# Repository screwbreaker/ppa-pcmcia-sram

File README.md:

# SAKURA, Amiga pcmcia sram
4MB of Fast RAM for unexpanded Amiga 600/1200.
Original desig by Jarosław Bieliński and Radosław Kujawa.
The informations about the original version of this board can be found here: https://github.com/Sakura-IT/ppa-pcmcia-sram

Since the original version, some components, like the RAM, are became difficult to find, so, many revisions of this board was made in order to use available components.
In 2018 the project was updated again and ported to KiCad by jensma: https://github.com/jensma/ppa-pcmcia-sram
This revision is based on his work.

### Summary
Some components like the RAM are available but not cheap. On the jensma revision also the PCB was not cheap, because he used small tracks and vias.
The main goal of this revision is to made the PCB as cheaper as possible. This make this expansion a little more affordable.

#### BOM
- C14,C3,C5,C6,C7,C8,C9,C10,C11,C12,C13,C4 100nF 0805 ceramic capacitor
- C1,C2: >=10uF >=6,3V 1206 tantalum capacitor
- U1: LM1117-3.3 voltage regulator
- IC2,IC3, IC4 74LCX245MTC
- IC5,IC6,IC7: 74LCX541TTR
- IC1: AS6C3216-55, SRAM
- IC8: XC9536XL_44VQ CPLD
- PCMCIA connector 95622-004LF
- SW1: SW_SPDT_CK-JS102011SAQN

### Installation
Since this board don't have a proper PCMCIA case it must be inserted carefully.
Do not apply too much force, or the pin iside the Amiga connector can be damaged.
There is a maker on the board to identify the upper side.

### License
This board is Open Hardware. If you make any modifications to the board, please contribute them back.

### Disclaimer
This board is provided to you 'as is' and without any express or implied warranties whatsoever with respect to its functionality, operability or use, including, without limitation, any implied warranties of merchantability, fitness for a particular purpose or infringement. We expressly disclaim any liability whatsoever for any direct, indirect, consequential, incidental or special damages, including, without limitation, lost revenues, lost profits, losses resulting from business interruption or loss of data, regardless of the form of action or legal theory under which the liability may be asserted, even if advised of the possibility or likelihood of such damages.

### Thanks
- A special Thanks to: [EmberHeavyIndustries](https://github.com/EmberHeavyIndustries) for the help in the development.
- DanyPPC who started the discussion, [SukkoPera](https://github.com/SukkoPera), Mck, and all the other guys on the Italian Amiga forum [Amigapage](https://www.amigapage.it/index.php?op=v&pl=forum&id=F012019-2-9&page=1)

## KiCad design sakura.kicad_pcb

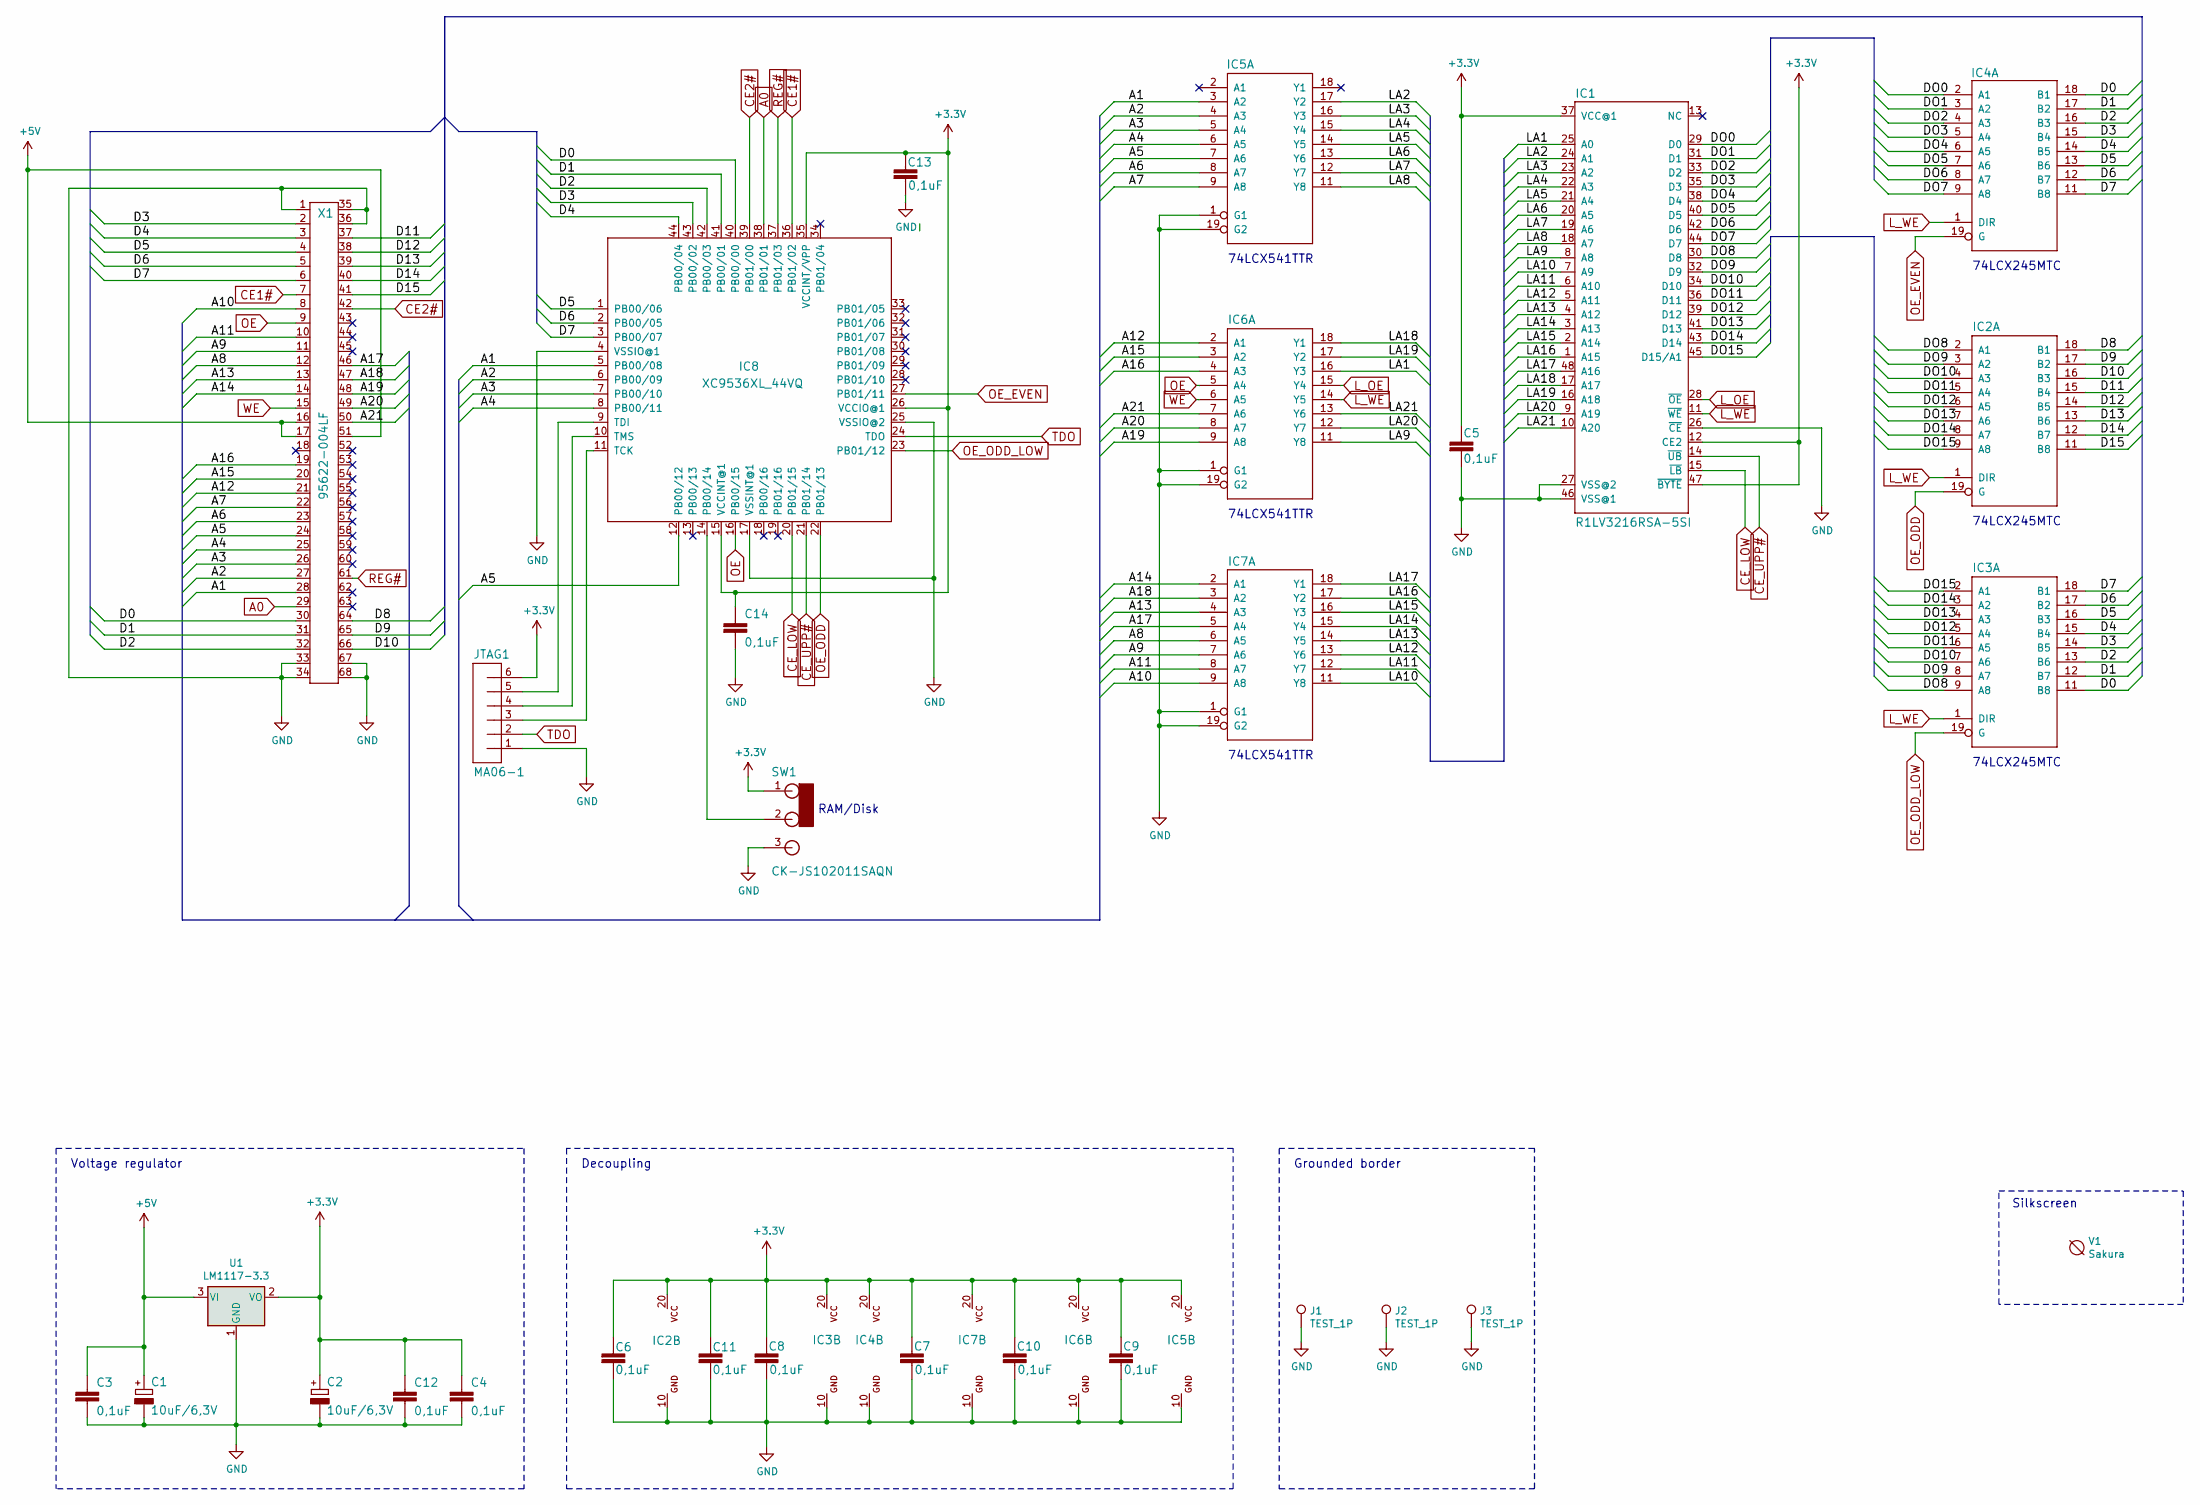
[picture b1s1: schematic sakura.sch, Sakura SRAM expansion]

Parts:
C1, C2: 10uF/6,3V; C_1206_HandSoldering
C3, C4, C5, C6, C7, C8, C9, C10, C11, C12, C13, C14: 0,1uF; C_0805_HandSoldering
IC1: R1LV3216RSA-5SI; TSOP-I-48_18.4x12mm_Pitch0.5mm
IC2, IC3, IC4: 74LCX245MTC; SSOP-20_5.3x7.2mm_Pitch0.65mm
IC5, IC6, IC7: 74LCX541TTR; SSOP-20_5.3x7.2mm_Pitch0.65mm
IC8: XC9536XL_44VQ; TQFP-44_10x10mm_Pitch0.8mm
J1, J2, J3: TEST_1P; viabar
JTAG1: MA06-1; Socket_Strip_Straight_1x06_Pitch2.54mm
SW1: CK-JS102011SAQN; SW_SPDT_CK-JS102011SAQN
U1: LM1117-3.3; SOT-223-3_TabPin2
V1: Sakura; logo
X1: 95622-004LF; pcmcia

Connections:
+3V3: C2.1 (+), C4.1, C5.1, C6.1, C7.1, C8.1, C9.1, C10.1, C11.1, C12.1, C13.1, C14.1, IC1.12 (CE2), IC1.37 (VCC@1), IC1.47 (~BYTE), IC2.20 (VCC), IC3.20 (VCC), IC4.20 (VCC), IC5.20 (VCC), IC6.20 (VCC), IC7.20 (VCC), IC8.15 (VCCINT@1), IC8.26 (VCCIO@1), IC8.35 (VCCINT/VPP), JTAG1.6, SW1.1, U1.2 (VO)
+5V: C1.1 (+), C3.1, U1.3 (VI), X1.16, X1.17, X1.51
/A1: IC5.3 (A2), IC8.5 (PB00/08), X1.28
/A2: IC5.4 (A3), IC8.6 (PB00/09), X1.27
/A3: IC5.5 (A4), IC8.7 (PB00/10), X1.26
/A4: IC5.6 (A5), IC8.8 (PB00/11), X1.25
/A5: IC5.7 (A6), IC8.12 (PB00/12), X1.24
/A6: IC5.8 (A7), X1.23
/A7: IC5.9 (A8), X1.22
/A8: IC7.6 (A5), X1.12
/A9: IC7.7 (A6), X1.11
/A10: IC7.9 (A8), X1.8
/A11: IC7.8 (A7), X1.10
/A12: IC6.2 (A1), X1.21
/A13: IC7.4 (A3), X1.13
/A14: IC7.2 (A1), X1.14
/A15: IC6.3 (A2), X1.20
/A16: IC6.4 (A3), X1.19
/A17: IC7.5 (A4), X1.46
/A18: IC7.3 (A2), X1.47
/A19: IC6.9 (A8), X1.48
/A20: IC6.8 (A7), X1.49
/A21: IC6.7 (A6), X1.50
/D0: IC3.11 (B8), IC4.18 (B1), IC8.40 (PB00/00), X1.30
/D1: IC3.12 (B7), IC4.17 (B2), IC8.41 (PB00/01), X1.31
/D2: IC3.13 (B6), IC4.16 (B3), IC8.42 (PB00/03), X1.32
/D3: IC3.14 (B5), IC4.15 (B4), IC8.43 (PB00/02), X1.2
/D4: IC3.15 (B4), IC4.14 (B5), IC8.44 (PB00/04), X1.3
/D5: IC3.16 (B3), IC4.13 (B6), IC8.1 (PB00/06), X1.4
/D6: IC3.17 (B2), IC4.12 (B7), IC8.2 (PB00/05), X1.5
/D7: IC3.18 (B1), IC4.11 (B8), IC8.3 (PB00/07), X1.6
/D8: IC2.18 (B1), X1.64
/D9: IC2.17 (B2), X1.65
/D10: IC2.16 (B3), X1.66
/D11: IC2.15 (B4), X1.37
/D12: IC2.14 (B5), X1.38
/D13: IC2.13 (B6), X1.39
/D14: IC2.12 (B7), X1.40
/D15: IC2.11 (B8), X1.41
/DO0: IC1.29 (D0), IC4.2 (A1)
/DO1: IC1.31 (D1), IC4.3 (A2)
/DO2: IC1.33 (D2), IC4.4 (A3)
/DO3: IC1.35 (D3), IC4.5 (A4)
/DO4: IC1.38 (D4), IC4.6 (A5)
/DO5: IC1.40 (D5), IC4.7 (A6)
/DO6: IC1.42 (D6), IC4.8 (A7)
/DO7: IC1.44 (D7), IC4.9 (A8)
/DO8: IC1.30 (D8), IC2.2 (A1), IC3.9 (A8)
/DO9: IC1.32 (D9), IC2.3 (A2), IC3.8 (A7)
/DO10: IC1.34 (D10), IC2.4 (A3), IC3.7 (A6)
/DO11: IC1.36 (D11), IC2.5 (A4), IC3.6 (A5)
/DO12: IC1.39 (D12), IC2.6 (A5), IC3.5 (A4)
/DO13: IC1.41 (D13), IC2.7 (A6), IC3.4 (A3)
/DO14: IC1.43 (D14), IC2.8 (A7), IC3.3 (A2)
/DO15: IC1.45 (D15/A1), IC2.9 (A8), IC3.2 (A1)
/LA1: IC1.25 (A0), IC6.16 (Y3)
/LA2: IC1.24 (A1), IC5.17 (Y2)
/LA3: IC1.23 (A2), IC5.16 (Y3)
/LA4: IC1.22 (A3), IC5.15 (Y4)
/LA5: IC1.21 (A4), IC5.14 (Y5)
/LA6: IC1.20 (A5), IC5.13 (Y6)
/LA7: IC1.19 (A6), IC5.12 (Y7)
/LA8: IC1.18 (A7), IC5.11 (Y8)
/LA9: IC1.8 (A8), IC6.11 (Y8)
/LA10: IC1.7 (A9), IC7.11 (Y8)
/LA11: IC1.6 (A10), IC7.12 (Y7)
/LA12: IC1.5 (A11), IC7.13 (Y6)
/LA13: IC1.4 (A12), IC7.14 (Y5)
/LA14: IC1.3 (A13), IC7.15 (Y4)
/LA15: IC1.2 (A14), IC7.16 (Y3)
/LA16: IC1.1 (A15), IC7.17 (Y2)
/LA17: IC1.48 (A16), IC7.18 (Y1)
/LA18: IC1.17 (A17), IC6.18 (Y1)
/LA19: IC1.16 (A18), IC6.17 (Y2)
/LA20: IC1.9 (A19), IC6.12 (Y7)
/LA21: IC1.10 (A20), IC6.13 (Y6)
A0: IC8.38 (PB01/01), X1.29
CE1#: IC8.36 (PB01/02), X1.7
CE2#: IC8.39 (PB01/00), X1.42
CE_LOW: IC1.15 (~LB), IC8.20 (PB01/15)
CE_UPP#: IC1.14 (~UB), IC8.21 (PB01/14)
GND: C1.2 (-), C2.2 (-), C3.2, C4.2, C5.2, C6.2, C7.2, C8.2, C9.2, C10.2, C11.2, C12.2, C13.2, C14.2, IC1.26 (~CE), IC1.27 (VSS@2), IC1.46 (VSS@1), IC2.10 (GND), IC3.10 (GND), IC4.10 (GND), IC5.1 (G1), IC5.10 (GND), IC5.19 (G2), IC6.1 (G1), IC6.10 (GND), IC6.19 (G2), IC7.1 (G1), IC7.10 (GND), IC7.19 (G2), IC8.4 (VSSIO@1), IC8.17 (VSSINT@1), IC8.25 (VSSIO@2), J1.1, J2.1, J3.1, JTAG1.1, SW1.3, U1.1 (GND), X1.1, X1.33, X1.34, X1.35, X1.36, X1.67, X1.68
L_OE: IC1.28 (~OE), IC6.15 (Y4)
L_WE: IC1.11 (~WE), IC2.1 (DIR), IC3.1 (DIR), IC4.1 (DIR), IC6.14 (Y5)
unnamed: IC8.9 (TDI), JTAG1.5
unnamed: IC8.10 (TMS), JTAG1.4
unnamed: IC8.11 (TCK), JTAG1.3
unnamed: IC8.14 (PB00/14), SW1.2
OE: IC6.5 (A4), IC8.16 (PB00/15), X1.9
OE_EVEN: IC4.19 (G), IC8.27 (PB01/11)
OE_ODD: IC2.19 (G), IC8.22 (PB01/13)
OE_ODD_LOW: IC3.19 (G), IC8.23 (PB01/12)
REG#: IC8.37 (PB01/03), X1.61
TDO: IC8.24 (TDO), JTAG1.2
WE: IC6.6 (A5), X1.15

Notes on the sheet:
74LCX541TTR
74LCX245MTC
Grounded border
Decoupling
Voltage regulator
Silkscreen
RAM/Disk

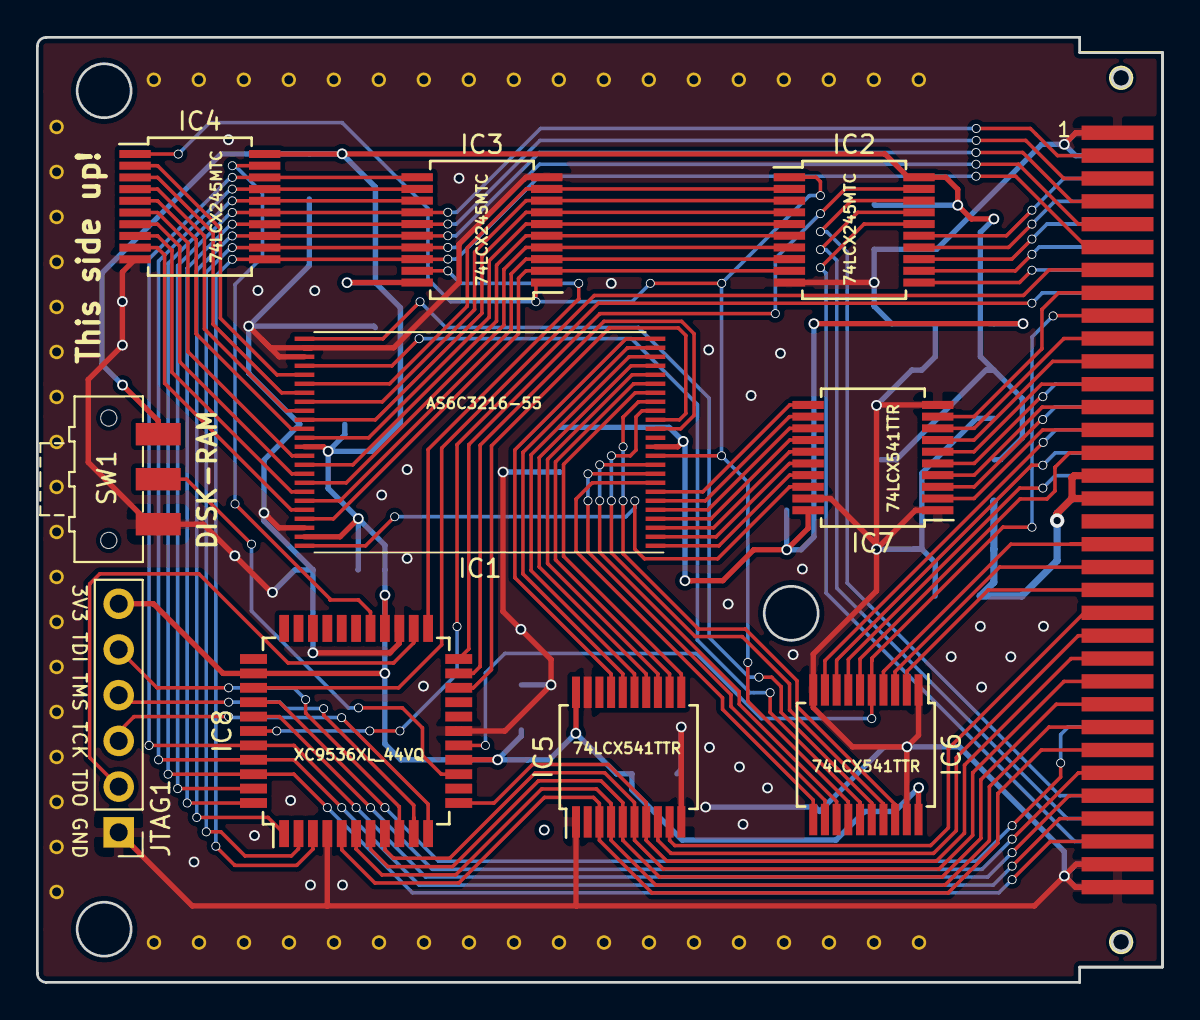
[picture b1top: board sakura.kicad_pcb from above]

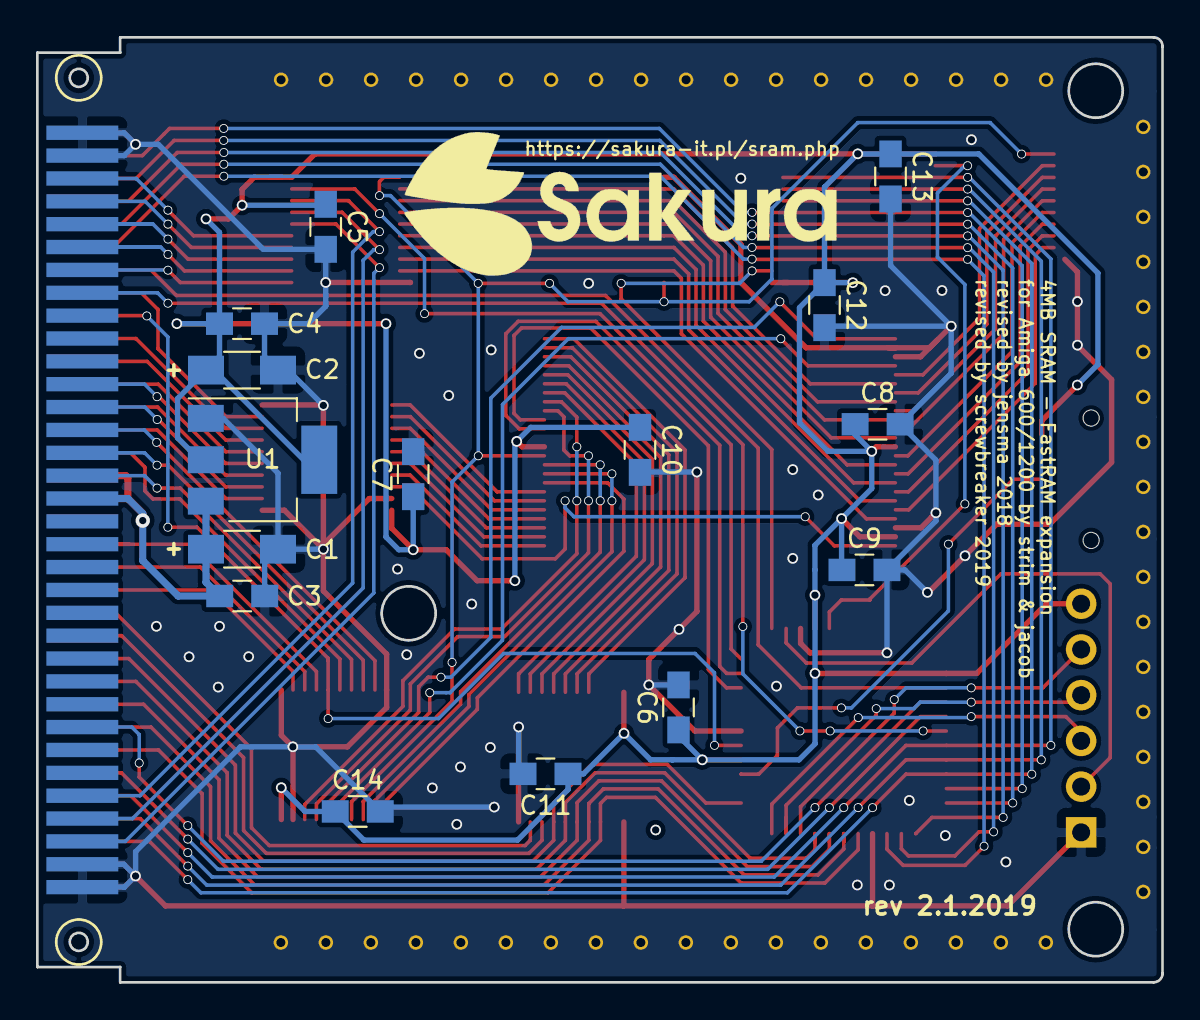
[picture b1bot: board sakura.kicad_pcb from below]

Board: 2 copper layers, 62.5 x 52.5 mm, 30 parts (16 on the bottom side), 95 nets.

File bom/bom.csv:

"Id";"Designator";"Package";"Quantity";"Designation";"Supplier and ref";
1;"SW1";"SW_SPDT_CK-JS102011SAQN";1;"RAM/Disk";;;
2;"C14,C3,C5,C6,C7,C8,C9,C10,C11,C12,C13,C4";"C_0805_HandSoldering";12;"0,1uF";;;
3;"C1,C2";"C_1206_HandSoldering";2;"10uF/6,3V";;;
4;"U1";"SOT-223-3_TabPin2";1;"LM1117-3.3";;;
5;"IC2,IC3,IC4";"SSOP-20_5.3x7.2mm_Pitch0.65mm";3;"74LCX245MTC";;;
6;"IC5,IC6,IC7";"SSOP-20_5.3x7.2mm_Pitch0.65mm";3;"74LCX541TTR";;;
7;"JTAG1";"Socket_Strip_Straight_1x06_Pitch2.54mm";1;"MA06-1";;;
8;"X1";"pcmcia";1;"PCMCIA female";;;
9;"IC1";"TSOP-I-48_18.4x12mm_Pitch0.5mm";1;"AS6C3216-55";;;
10;"IC8";"TQFP-44_10x10mm_Pitch0.8mm";1;"XC9536XL_44VQ";;;

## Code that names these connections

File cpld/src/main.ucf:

# control signals from PCMCIA
NET "ce1" LOC = "36";
NET "ce2" LOC = "39";
NET "a0" LOC = "38"; # address bus bit 0
NET "reg" LOC = "37";
NET "oe_rom" LOC = "16";  # OE from PCMCIA in fact only used by ROM

# switches/jumpers
NET "sw_rom" LOC = "14";

# control signals to memory
NET "oe_even" LOC = "27";
NET "oe_oddlow" LOC = "23";
NET "oe_odd" LOC = "22";
NET "ce_upp" LOC = "21";
NET "ce_low" LOC = "20";
NET "ce_attr_external" LOC = "19";

# address bus (in fact A1-A5)
NET "addr<0>" LOC = "5";
NET "addr<1>" LOC = "6";
NET "addr<2>" LOC = "7";
NET "addr<3>" LOC = "8";
NET "addr<4>" LOC = "12";

# lowest 8 bits of data bus
NET "data<0>" LOC = "40";
NET "data<1>" LOC = "41";
NET "data<2>" LOC = "42";
NET "data<3>" LOC = "43";
NET "data<4>" LOC = "44";
NET "data<5>" LOC = "1";
NET "data<6>" LOC = "2";
NET "data<7>" LOC = "3";

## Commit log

2018-10-30 Set theme jekyll-theme-minimal
2018-11-14 revised for 2018 + added kicad sources
2019-07-20 switch 3D model
2019-07-20 interactive BOM
2019-07-20 license file
2019-07-20 PCMCIA connector datasheet
2019-07-20 RAM datasheet
2019-07-20 RAM dataseet
2019-07-20 CPLD datasheet
2019-07-20 gerbers
